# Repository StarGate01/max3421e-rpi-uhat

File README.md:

# Raspberry Pi MAX3421E uHAT Hardware

A uHAT for the Raspberry Pi (Zero), which adds a second USB 2.0 controller over SPI, using the MAX3421E chip.

Also read my blog post for this project: https://chrz.de/2023/12/05/fido2-hardware-part-2-usb-host-circuit-boards/

KiCAD version 7 is used to edit the files. Inspired by the Mini USB Host Shield 2.0 (https://laborjag.com/venta/arduino/mini-usb-host-shield-2-0/).

## Setup with Raspberry Pi OS

See § "Compiling the MAX3421-HCD Kernel Driver" and § "Automatic Driver Loading and Device Tree Configuration" of my blog post at https://chrz.de/2023/11/07/fido2-protocol-translation-hardware/

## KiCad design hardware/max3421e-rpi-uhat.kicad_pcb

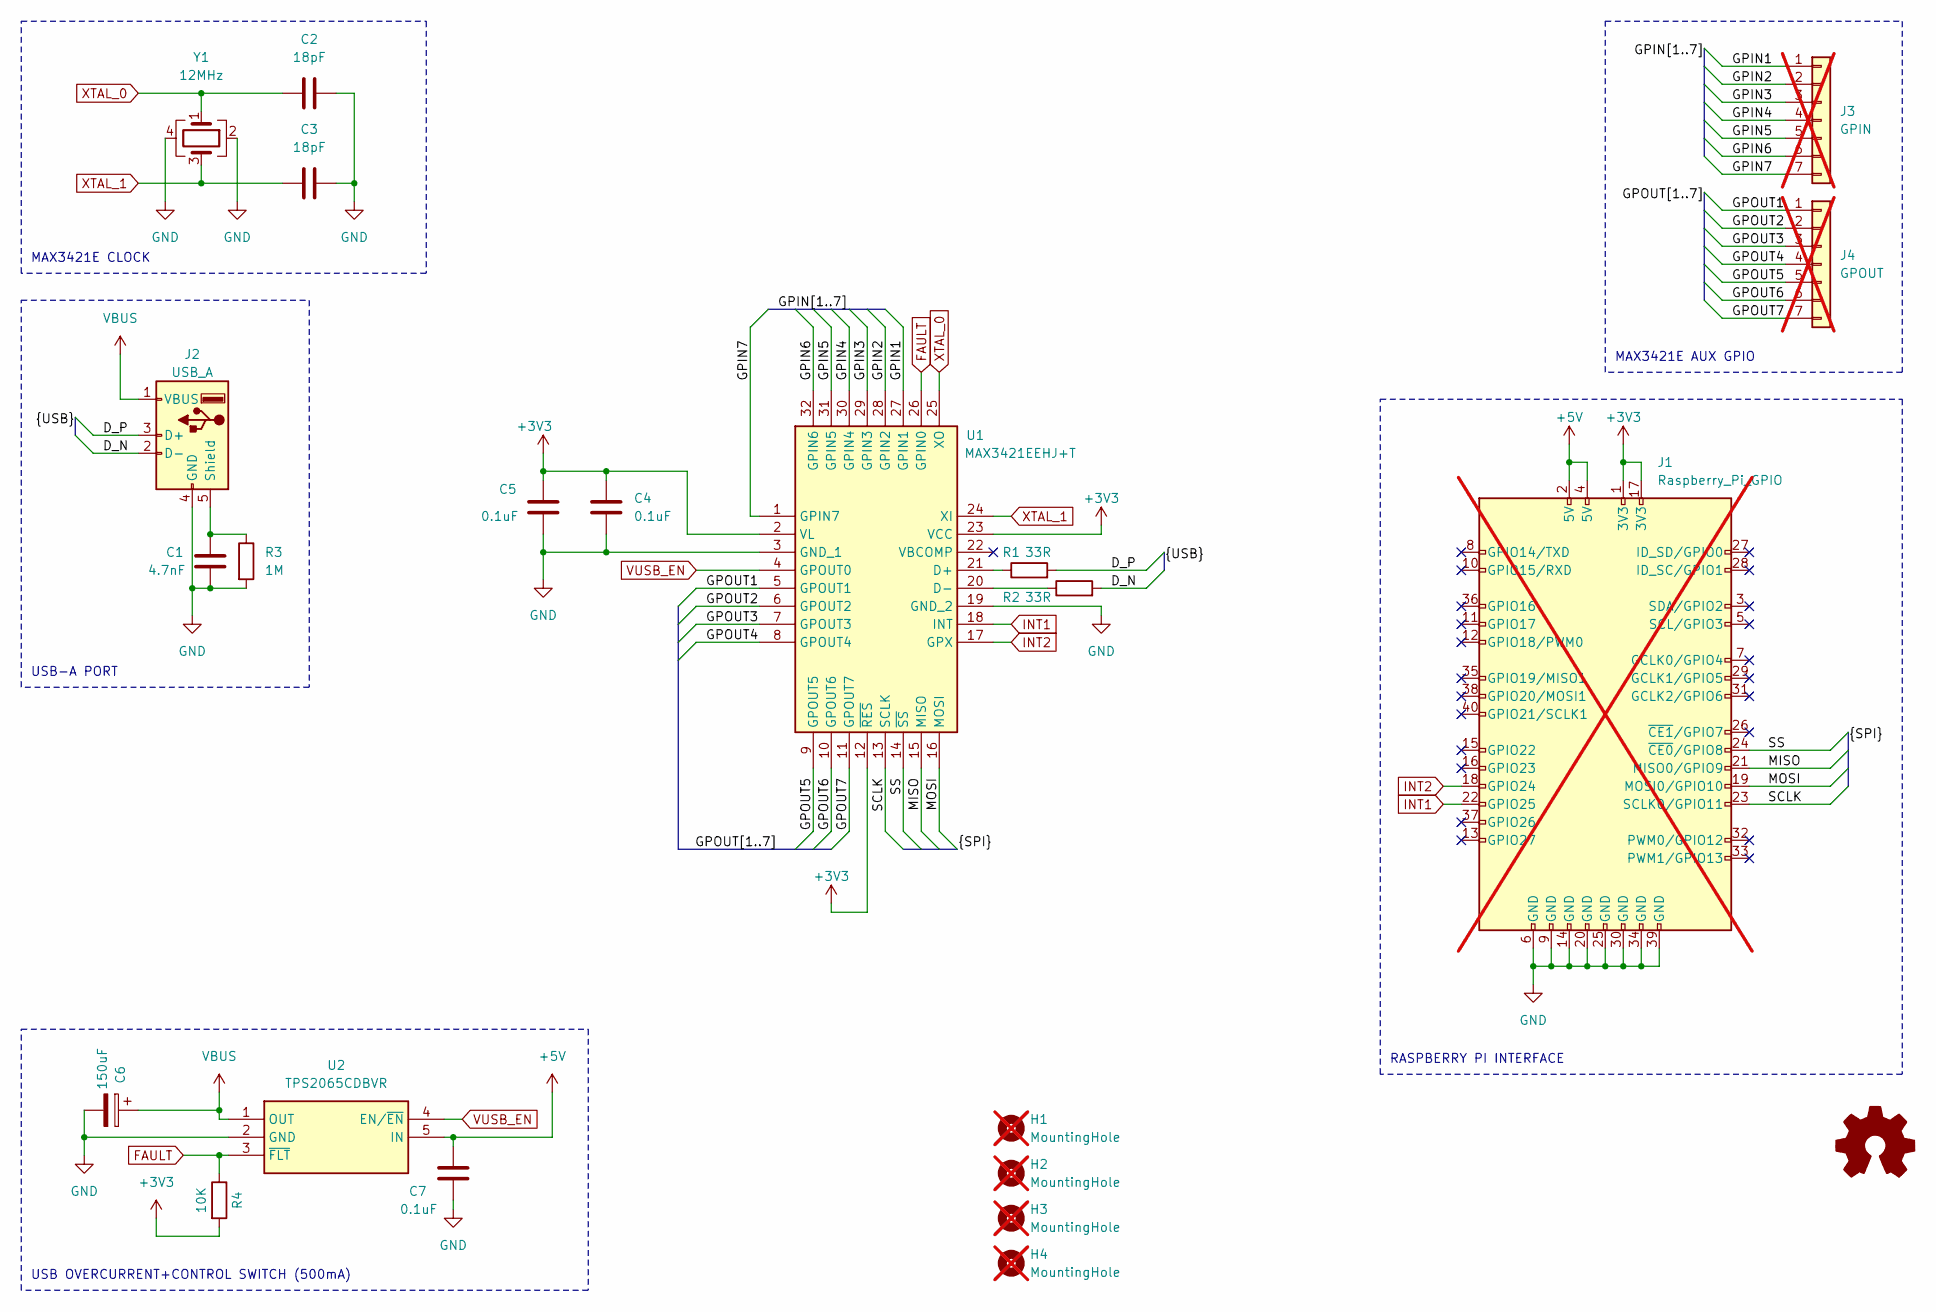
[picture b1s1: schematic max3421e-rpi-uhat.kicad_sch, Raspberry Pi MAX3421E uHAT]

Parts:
C1: 4.7nF; C_0603_1608Metric; MPN TBD
C2, C3: 18pF; C_0603_1608Metric; MPN TBD
C4, C5: 0.1uF; C_0603_1608Metric; MPN TBD
C6: 150uF; CP_Elec_6.3x5.4; MPN TBD
C7: 0.1uF; C_0603_1608Metric
H1, H2, H3, H4: MountingHole; MountingHole_2.75mm_6.2mm; MPN N/A; not fitted
J1: Raspberry_Pi_GPIO; PinSocket_2x20_P2.54mm_Vertical; MPN N/A; not fitted
J2: USB_A; USB-A-SMD_FUS270-FSBW5K; MPN 904-131A2032S10100
J3: GPIN; PinHeader_1x07_P2.54mm_Vertical; MPN N/A; not fitted
J4: GPOUT; PinHeader_1x07_P2.54mm_Vertical; MPN N/A; not fitted
R1, R2: 33R; R_0603_1608Metric; MPN TBD
R3: 1M; R_0603_1608Metric; MPN TBD
R4: 10K; R_0603_1608Metric
U1: MAX3421EEHJ+T; QFP50P700X700X120-32N; MPN MAX3421EEHJ+T
U2: TPS2065CDBVR; SOT95P280X145-5N; MPN TPS2065CDBVR
Y1: 12MHz; Crystal_SMD_3225-4Pin_3.2x2.5mm; MPN TBD

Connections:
+3V3: C4.1, C5.1, J1.1 (3V3), J1.17 (3V3), R4.2, U1.2 (VL), U1.12 (~RES), U1.23 (VCC)
+5V: C7.1, J1.2 (5V), J1.4 (5V), U2.5 (IN)
/D_N: J2.2 (D-), R2.2
/D_P: J2.3 (D+), R1.2
/GPIN1: J3.1, U1.27 (GPIN1)
/GPIN2: J3.2, U1.28 (GPIN2)
/GPIN3: J3.3, U1.29 (GPIN3)
/GPIN4: J3.4, U1.30 (GPIN4)
/GPIN5: J3.5, U1.31 (GPIN5)
/GPIN6: J3.6, U1.32 (GPIN6)
/GPIN7: J3.7, U1.1 (GPIN7)
/GPOUT1: J4.1, U1.5 (GPOUT1)
/GPOUT2: J4.2, U1.6 (GPOUT2)
/GPOUT3: J4.3, U1.7 (GPOUT3)
/GPOUT4: J4.4, U1.8 (GPOUT4)
/GPOUT5: J4.5, U1.9 (GPOUT5)
/GPOUT6: J4.6, U1.10 (GPOUT6)
/GPOUT7: J4.7, U1.11 (GPOUT7)
/MISO: J1.21 (MISO0/GPIO9), U1.15 (MISO)
/MOSI: J1.19 (MOSI0/GPIO10), U1.16 (MOSI)
/SCLK: J1.23 (SCLK0/GPIO11), U1.13 (SCLK)
/SS: J1.24 (~CE0/GPIO8), U1.14 (~SS)
FAULT: R4.1, U1.26 (GPIN0), U2.3 (~FLT)
GND: C1.1, C2.1, C3.1, C4.2, C5.2, C6.2, C7.2, J1.6 (GND), J1.9 (GND), J1.14 (GND), J1.20 (GND), J1.25 (GND), J1.30 (GND), J1.34 (GND), J1.39 (GND), J2.4 (GND), R3.2, U1.3 (GND_1), U1.19 (GND_2), U2.2 (GND), Y1.2, Y1.4
INT1: J1.22 (GPIO25), U1.18 (INT)
INT2: J1.18 (GPIO24), U1.17 (GPX)
unnamed: C1.2, J2.5 (Shield), R3.1
unnamed: R1.1, U1.21 (D+)
unnamed: R2.1, U1.20 (D-)
VBUS: C6.1, J2.1 (VBUS), U2.1 (OUT)
VUSB_EN: U1.4 (GPOUT0), U2.4 (EN/~EN)
XTAL_0: C2.2, U1.25 (XO), Y1.1
XTAL_1: C3.2, U1.24 (XI), Y1.3

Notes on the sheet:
RASPBERRY PI INTERFACE
MAX3421E AUX GPIO
MAX3421E CLOCK
USB-A PORT
USB OVERCURRENT+CONTROL SWITCH (500mA)

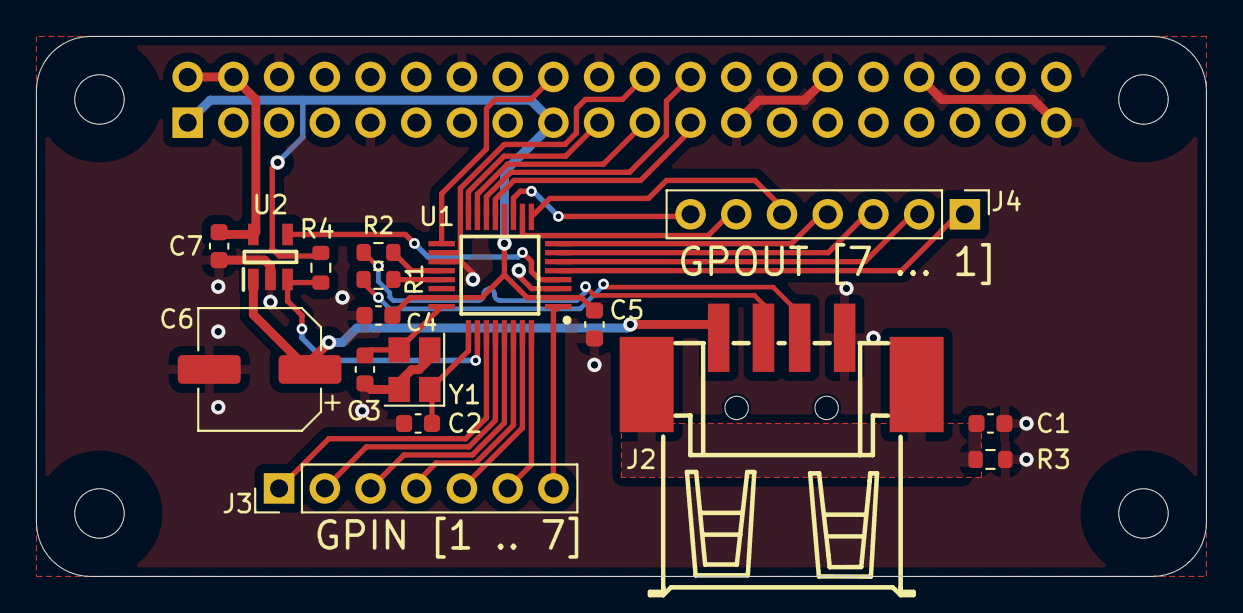
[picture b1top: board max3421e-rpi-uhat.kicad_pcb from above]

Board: 2 copper layers, 65.0 x 30.0 mm, 22 parts (1 on the bottom side), 33 nets.

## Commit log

2023-11-11 init project and add docs
2023-11-11 set up board
2023-11-12 Design version 1.0
2023-11-12 Export version 1.0
2023-12-05 fix bom
2023-12-05 remove old files
